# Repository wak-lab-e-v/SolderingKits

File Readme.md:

# SolderingKits

## Little Robot
EN: Small soldering exercise for the simple circuit with 4 LEDs, 2 switches 4 resistors and a button cell CR2032

DE: Kleine Lötübung für den einfachen Stromkreis mit  4 LEDs , 2 Schalter 4 Widerstände und eine Knopfzelle CR2032

[README](LittleRobot/Readme.md) 

[PDF](LittleRobot/tex/LittleRobot_assembly.pdf)

Design: Martin Hildebrandt
licensed CC BY

Logo: By Dorothea Wendt
licensed CC BY-ND

## RoBadge#1

By Bluino

[README](RoBadge%231/Readme.md)

[PDF](RoBadge%231/tex/RoBadge%231.pdf)
 
Robadge#1 Robadge%231
## LedEgg

Design: Martin Hildebrandt
licensed CC BY

[Detail](LedEgg/README.md)

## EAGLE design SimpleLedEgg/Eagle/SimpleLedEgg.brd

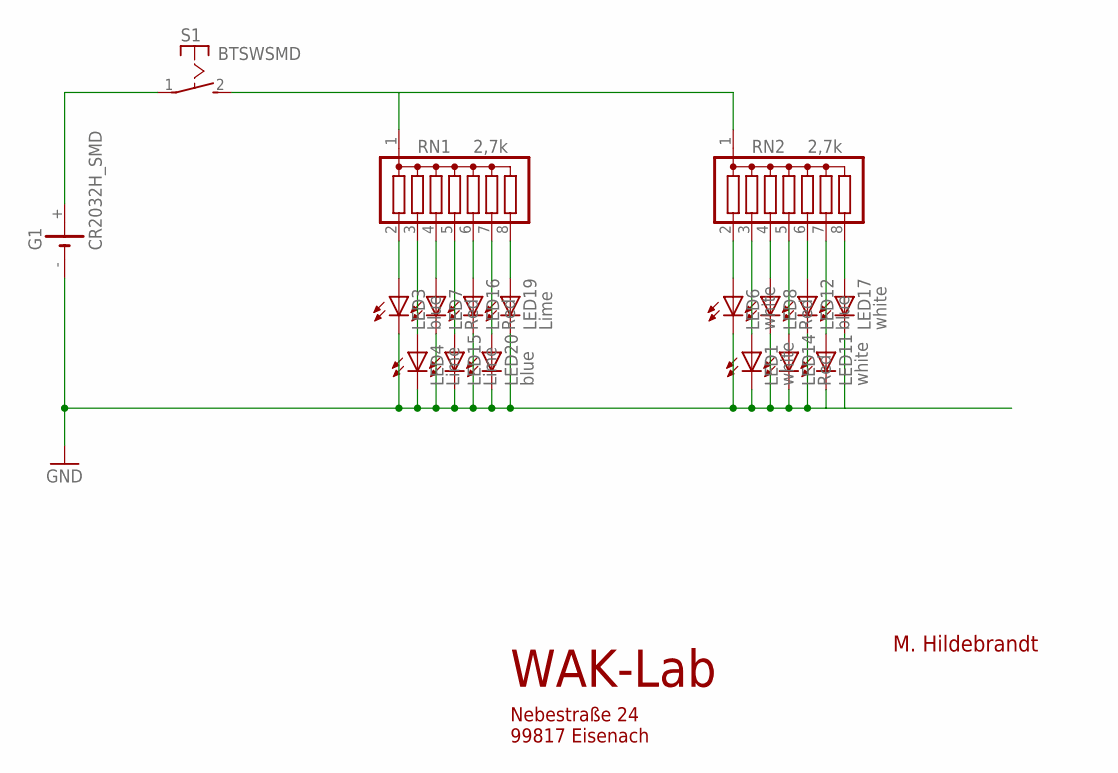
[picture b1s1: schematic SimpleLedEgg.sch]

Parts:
G1: CR2032H_SMD
LED1, LED6, LED11, LED17: white; LED3MM
LED3, LED12, LED20: blue; LED3MM
LED4, LED15, LED19: Lime; LED3MM
LED7, LED8, LED14, LED16: Red; LED3MM
RN1, RN2: 2,7k; SIL8
S1: BTSWSMD; BTSW_SMD

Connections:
GND: G1.-, LED1.K (C), LED3.K (C), LED4.K (C), LED6.K (C), LED7.K (C), LED8.K (C), LED11.K (C), LED12.K (C), LED14.K (C), LED15.K (C), LED16.K (C), LED17.K (C), LED19.K (C), LED20.K (C)
unnamed: RN1.1, RN2.1, S1.2 (S)
unnamed: LED3.A, RN1.2
unnamed: LED4.A, RN1.3
unnamed: LED7.A, RN1.4
unnamed: LED15.A, RN1.5
unnamed: LED16.A, RN1.6
unnamed: LED20.A, RN1.7
unnamed: LED19.A, RN1.8
unnamed: LED6.A, RN2.2
unnamed: LED1.A, RN2.3
unnamed: LED8.A, RN2.4
unnamed: LED12.A, RN2.6
unnamed: LED14.A, RN2.5
unnamed: LED11.A, RN2.7
unnamed: LED17.A, RN2.8
unnamed: G1.+, S1.1

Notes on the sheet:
M. Hildebrandt
WAK-Lab
Nebestraße 24 99817 Eisenach

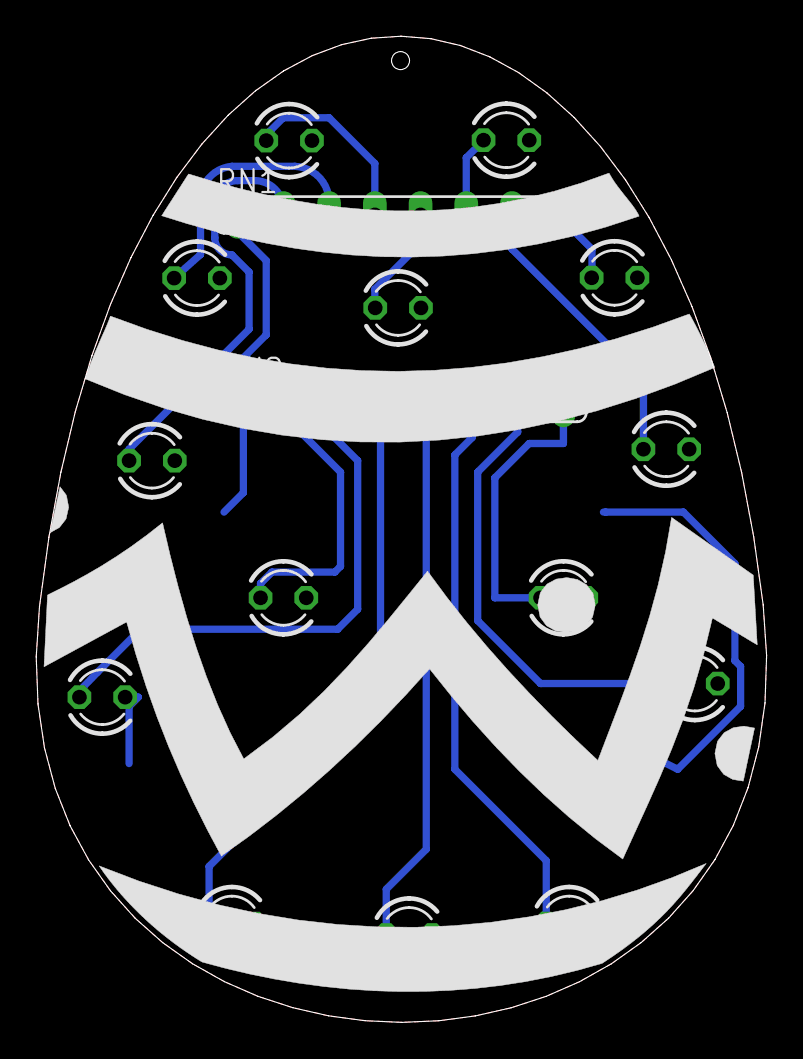
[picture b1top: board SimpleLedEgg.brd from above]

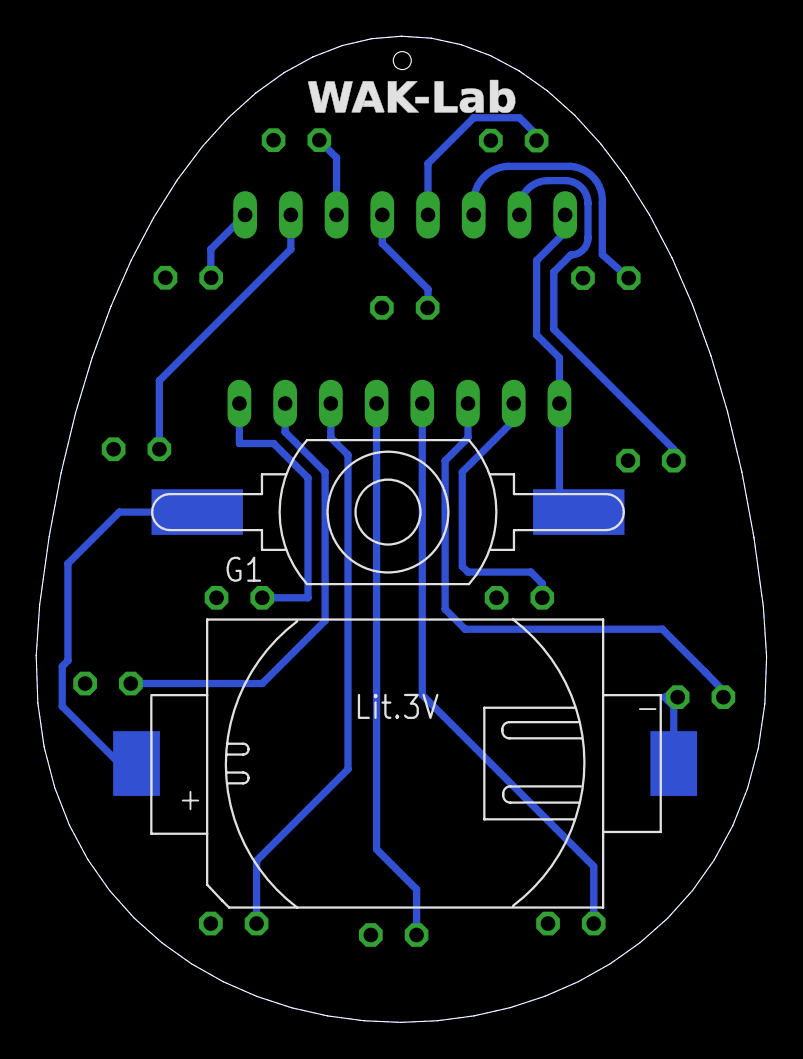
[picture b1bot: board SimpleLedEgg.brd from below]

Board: 2 copper layers, 40.6 x 54.8 mm, 18 parts (2 on the bottom side), 17 nets.

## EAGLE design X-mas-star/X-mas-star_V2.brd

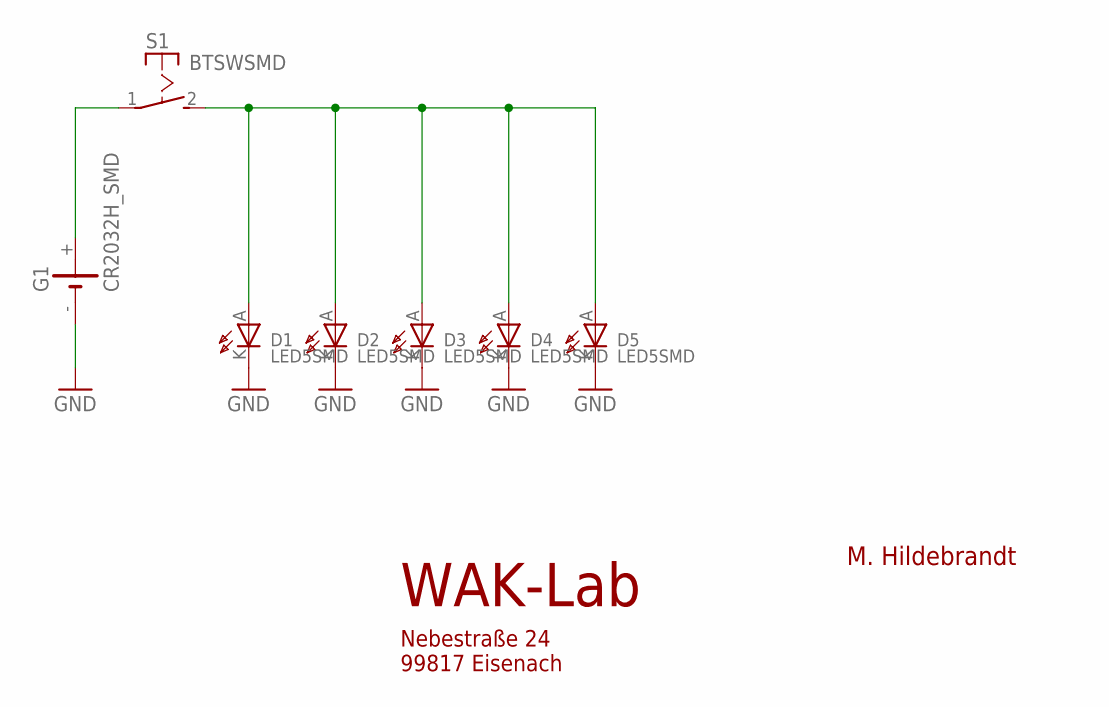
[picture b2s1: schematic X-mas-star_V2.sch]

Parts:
D1, D2, D3, D4, D5: LED5SMD; LED5MM_PADS
G1: CR2032H_SMD
S1: BTSWSMD; BTSW_SMD

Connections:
GND: D1.K, D2.K, D3.K, D4.K, D5.K, G1.-
unnamed: D1.A, D2.A, D3.A, D4.A, D5.A, S1.2 (S)
unnamed: G1.+, S1.1

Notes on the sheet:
M. Hildebrandt
WAK-Lab
Nebestraße 24 99817 Eisenach

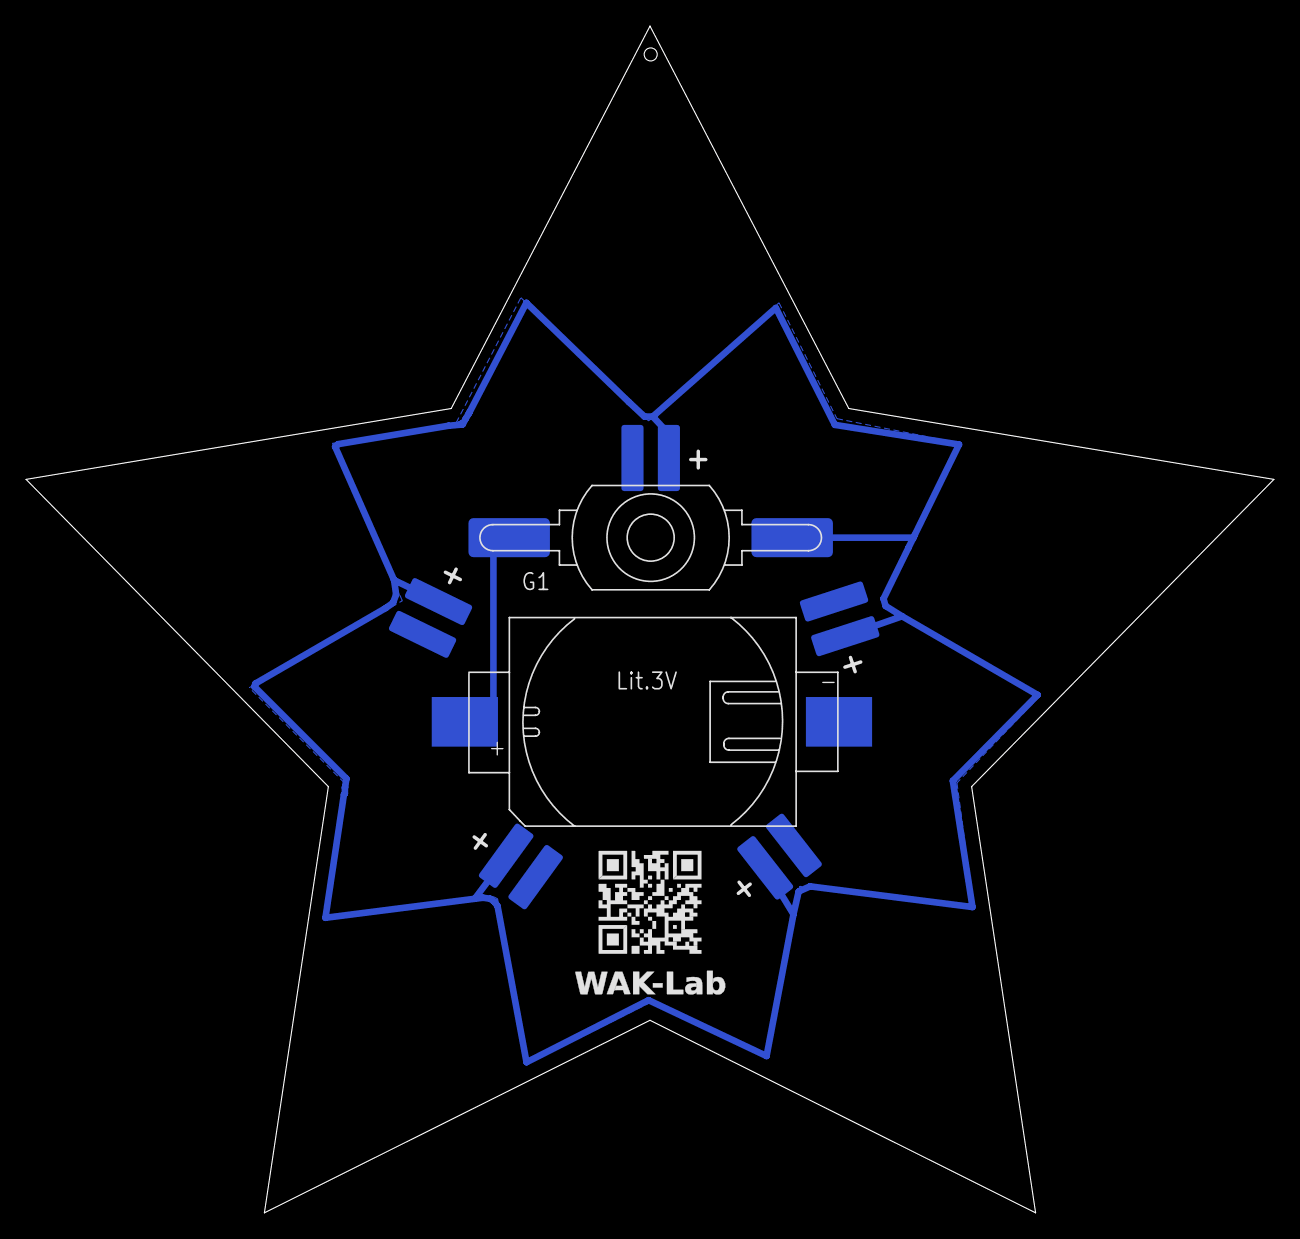
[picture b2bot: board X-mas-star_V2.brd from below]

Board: 2 copper layers, 95.7 x 91.0 mm, 7 parts (7 on the bottom side), 3 nets.

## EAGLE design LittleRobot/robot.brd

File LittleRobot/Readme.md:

# Little Robot  
 
EN: Small soldering exercise for the simple circuit with 4 LEDs, 2 switches 4 resistors and a button cell CR2032

DE: Kleine Lötübung für den einfachen Stromkreis mit  4 LEDs , 2 Schalter 4 Widerständen und eine Knopfzelle CR2032

Design: Martin Hildebrandt
licensed CC BY

Logo: By Dorothea Wendt
licensed CC BY-ND

# Step by Step

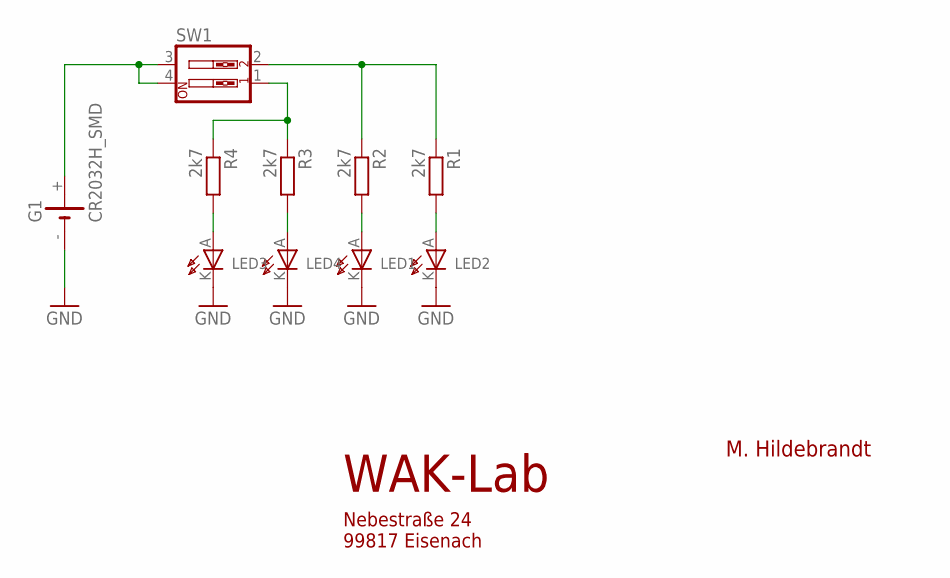
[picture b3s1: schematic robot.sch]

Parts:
G1: CR2032H_SMD
LED1, LED2: LEDREAR; 3MM_REAR
LED3, LED4: LED3MMH; 3MM_H
R1, R2, R3, R4: 2k7; 0204/7
SW1: SW_DIP-2; EDG-02

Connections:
GND: G1.-, LED1.K, LED2.K, LED3.K, LED4.K
unnamed: LED4.A, R3.2
unnamed: LED3.A, R4.2
unnamed: R1.1, R2.1, SW1.2
unnamed: R3.1, R4.1, SW1.1
unnamed: G1.+, SW1.3, SW1.4
unnamed: LED1.A, R2.2
unnamed: LED2.A, R1.2

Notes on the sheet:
M. Hildebrandt
WAK-Lab
Nebestraße 24 99817 Eisenach

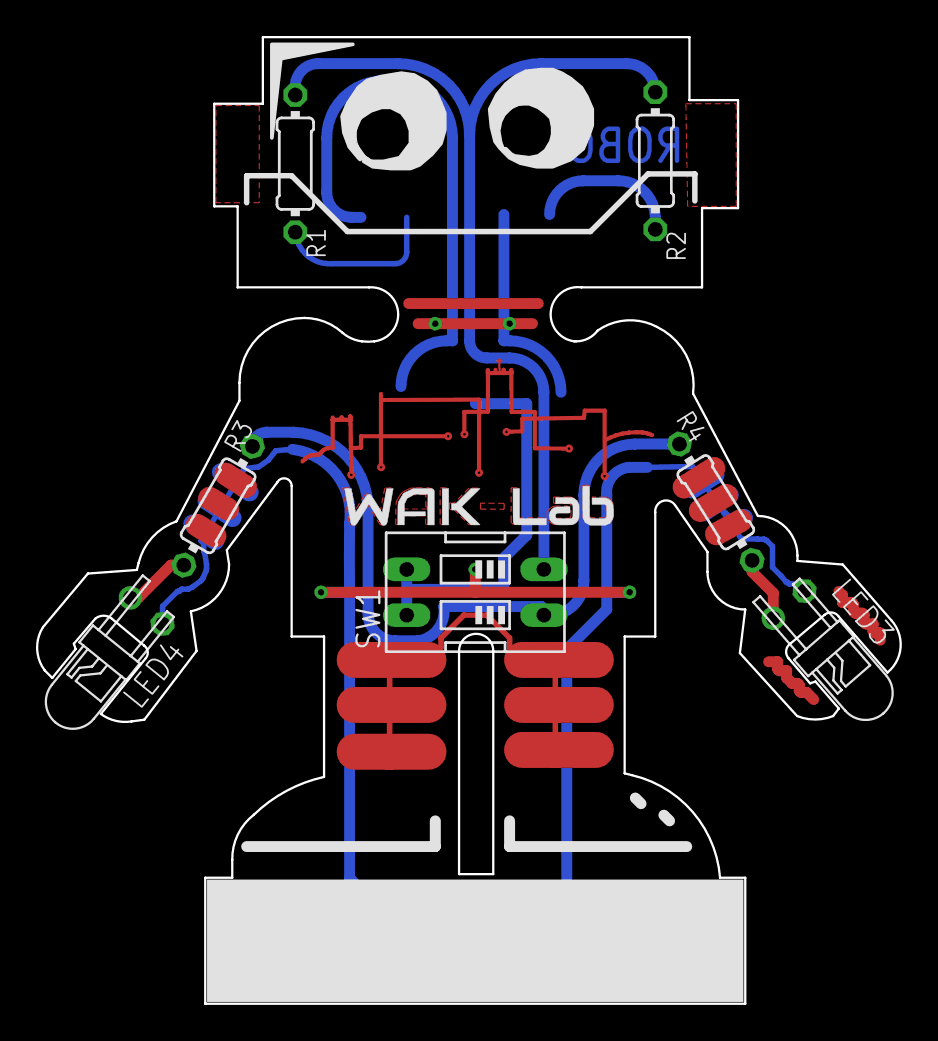
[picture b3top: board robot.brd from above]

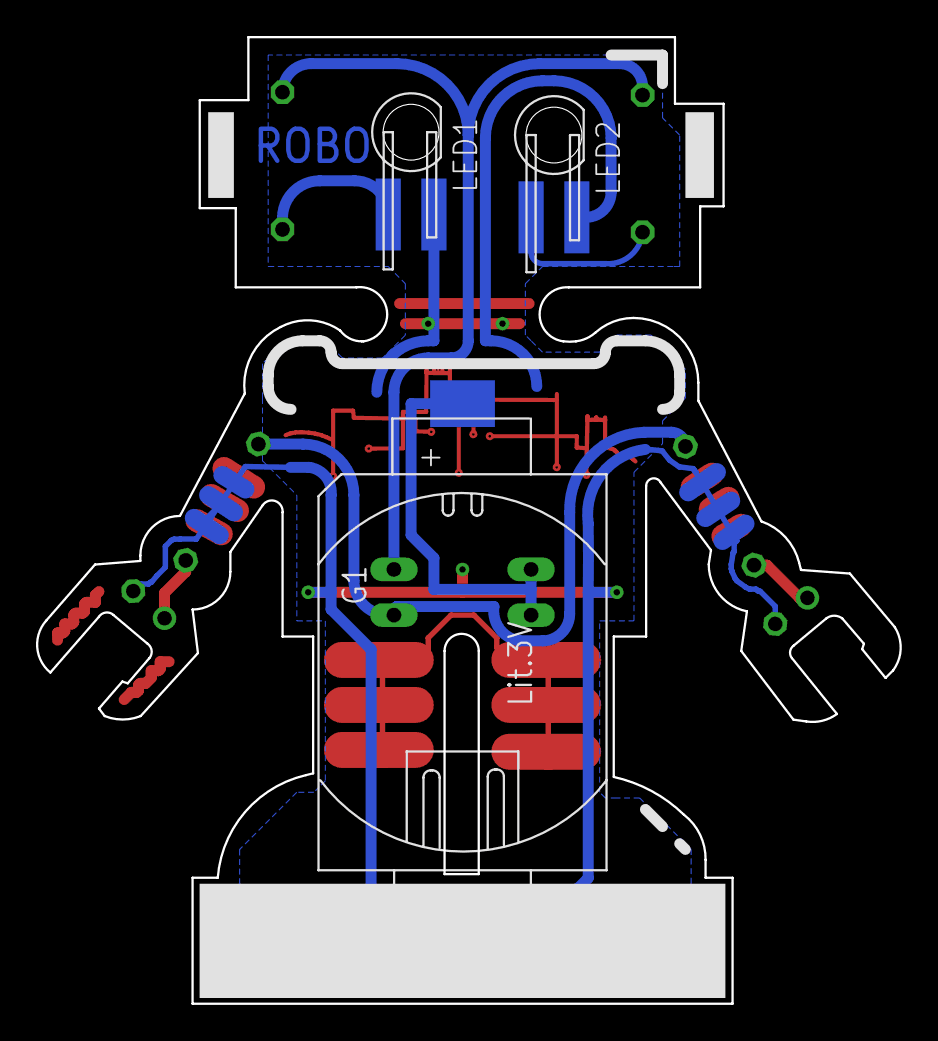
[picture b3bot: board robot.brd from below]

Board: 2 copper layers, 48.0 x 53.7 mm, 10 parts (3 on the bottom side), 8 nets.

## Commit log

2022-11-02 Schematic
2022-11-02 Licence
2022-11-03 Tot und Bottom Doc
2022-11-03 Eagle files with names and values
2023-03-10 Bilder hinzugefügt
2023-03-10 Resized Pictures
2023-03-10 Resize pictures
2023-03-10 Seperate README
2023-03-10 FIx Link
2023-03-10 Fix Links
2023-03-10 Assembly
2023-03-11 Anleitung
2023-03-11 Erste Korrektur
2023-03-12 Text überarbeitet
2023-03-12 LedEgg
2023-03-13 RoBadge#1
2023-03-13 Fix2
2023-03-15 Korrekturen
2023-03-25 Little Robot Batterypack & WAK-LAB Logo
2023-03-25 Gerber
2023-04-12 Image
2023-10-25 Copper Background
2024-11-13 Star and Simple EGG
